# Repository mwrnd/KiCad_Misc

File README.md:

# KiCad_Misc

Miscellaneous KiCad designs.

## MCP2221A_USB-C

[MCP2221A_USB-C](MCP2221A_USB-C) is a partially complete copy of the [Adafruit 4471 MCP2221A Breakout](https://www.adafruit.com/product/4471) I began adding to a project but [I ended up using the complete module](https://github.com/mwrnd/AlveoU25_JTAG_Adapter) instead.

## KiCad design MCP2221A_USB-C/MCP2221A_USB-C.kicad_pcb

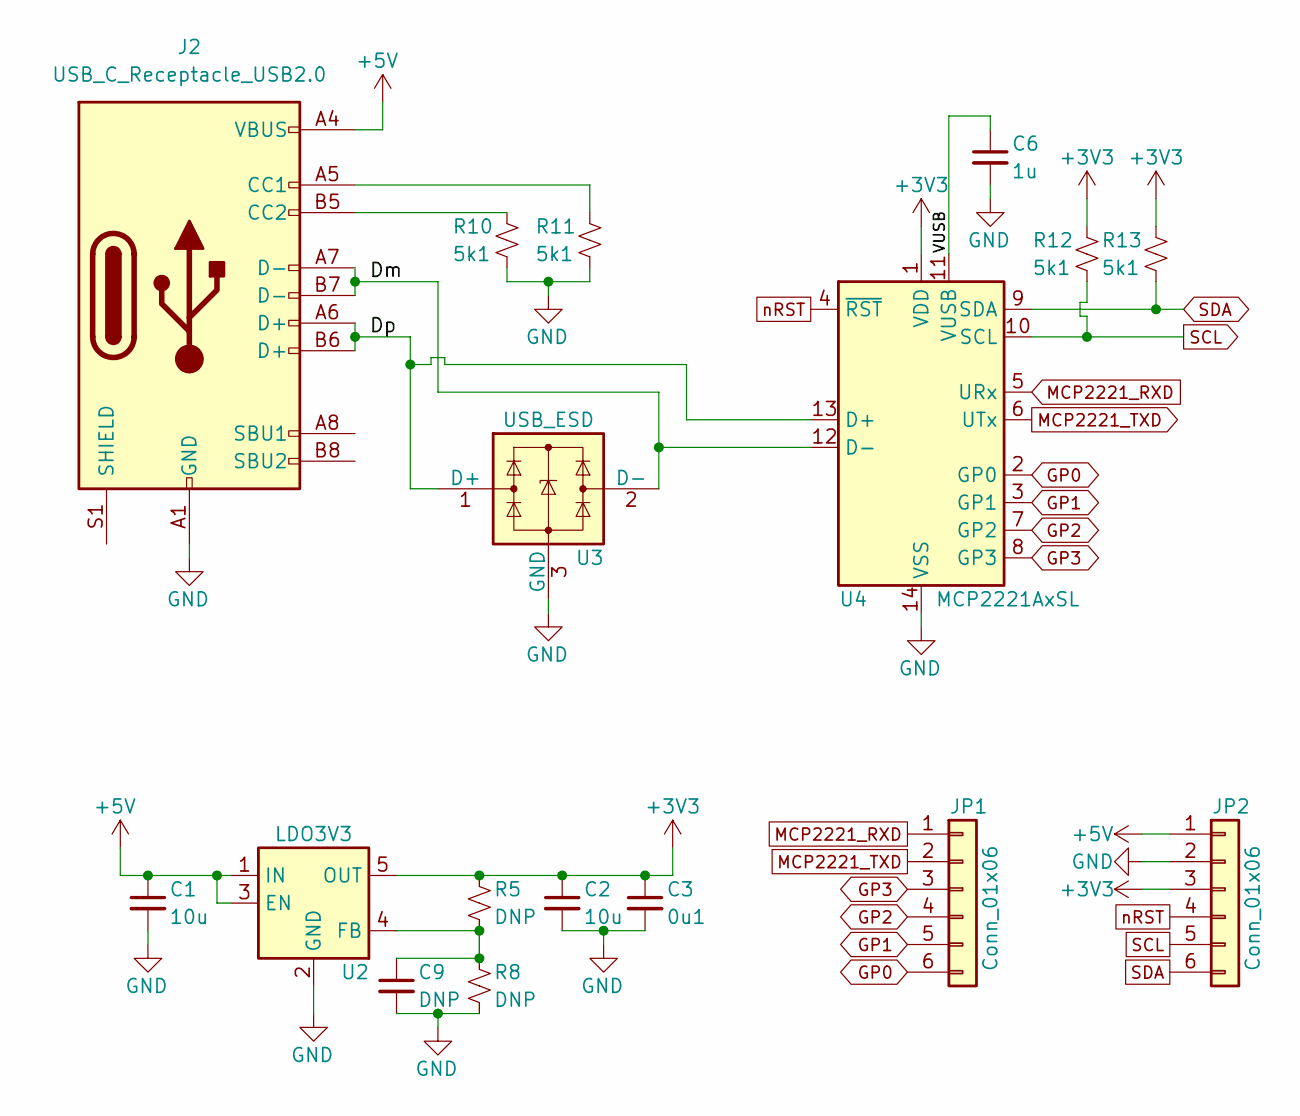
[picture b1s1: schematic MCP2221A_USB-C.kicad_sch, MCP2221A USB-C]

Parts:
C1, C2: 10u; C_0603_1608Metric_Pad1.08x0.95mm_HandSolder
C3: 0u1; C_0603_1608Metric_Pad1.08x0.95mm_HandSolder
C6: 1u; C_0603_1608Metric_Pad1.08x0.95mm_HandSolder
C9: DNP; C_0603_1608Metric_Pad1.08x0.95mm_HandSolder
J2: USB_C_Receptacle_USB2.0; USB_C_Receptacle_GCT_USB4105-xx-A_16P_TopMnt_Horizontal
JP1, JP2: Conn_01x06; PinSocket_1x06_P2.54mm_Vertical
R5, R8: DNP; R_0603_1608Metric_Pad0.98x0.95mm_HandSolder
R10, R11, R12, R13: 5k1; R_0603_1608Metric_Pad0.98x0.95mm_HandSolder
U2: LDO3V3; SOT-23-5
U3: USB_ESD; TSOT-23
U4: MCP2221AxSL; SOIC-14_3.9x8.7mm_P1.27mm

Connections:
+3V3: C2.1, C3.1, JP2.3, R5.1, R12.1, R13.1, U2.5 (OUT), U4.1 (VDD)
+5V: C1.1, J2.A4 (VBUS), J2.A9 (VBUS), J2.B4 (VBUS), J2.B9 (VBUS), JP2.1, U2.1 (IN), U2.3 (EN)
/Dm: J2.A7 (D-), J2.B7 (D-), U3.2 (D-), U4.12 (D-)
/Dp: J2.A6 (D+), J2.B6 (D+), U3.1 (D+), U4.13 (D+)
/VUSB: C6.1, U4.11 (VUSB)
GND: C1.2, C2.2, C3.2, C6.2, C9.2, J2.A1 (GND), J2.A12 (GND), J2.B1 (GND), J2.B12 (GND), JP2.2, R8.2, R10.2, R11.2, U2.2 (GND), U3.3 (GND), U4.14 (VSS)
GP0: JP1.6, U4.2 (GP0)
GP1: JP1.5, U4.3 (GP1)
GP2: JP1.4, U4.7 (GP2)
GP3: JP1.3, U4.8 (GP3)
MCP2221_RXD: JP1.1, U4.5 (URx)
MCP2221_TXD: JP1.2, U4.6 (UTx)
unnamed: J2.A5 (CC1), R11.1
unnamed: J2.B5 (CC2), R10.1
unnamed: C9.1, R5.2, R8.1, U2.4 (FB)
SCL: JP2.5, R12.2, U4.10 (SCL)
SDA: JP2.6, R13.2, U4.9 (SDA)
nRST: JP2.4, U4.4 (~RST)

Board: 2 copper layers, 17 parts (0 on the bottom side), 18 nets, no tracks yet.

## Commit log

2023-06-12 MCP2221A Schematic
